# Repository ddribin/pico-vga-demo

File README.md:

This repository contains the KiCad projects for the "VGA, SD card, and  audio demo boards for Raspberry Pi Pico and Raspberry Pi Pico W" from Chapter 3 of ["Hardware design with RP2040"][hw-design].

- `pico_vga_sd_aud`: Pico version
- `picow_vga_sd_aud`: Pico W version

This is based off of Version 2.2 of the document from 14 June, 2023, but contains some minor updates, such as saving with Version 7, the current version of KiCad.

The original KiCad project for the Pico version can be found at: https://datasheets.raspberrypi.com/rp2040/VGA-KiCAD.zip

The original KiCad project for the Pico W version can be found at: https://datasheets.raspberrypi.com/rp2040/VGA-PicoW-KiCAD.zip

The latest version of "Hardware design with RP2040" can be found at: https://datasheets.raspberrypi.com/rp2040/hardware-design-with-rp2040.pdf

[hw-design]: https://datasheets.raspberrypi.com/rp2040/hardware-design-with-rp2040.pdf

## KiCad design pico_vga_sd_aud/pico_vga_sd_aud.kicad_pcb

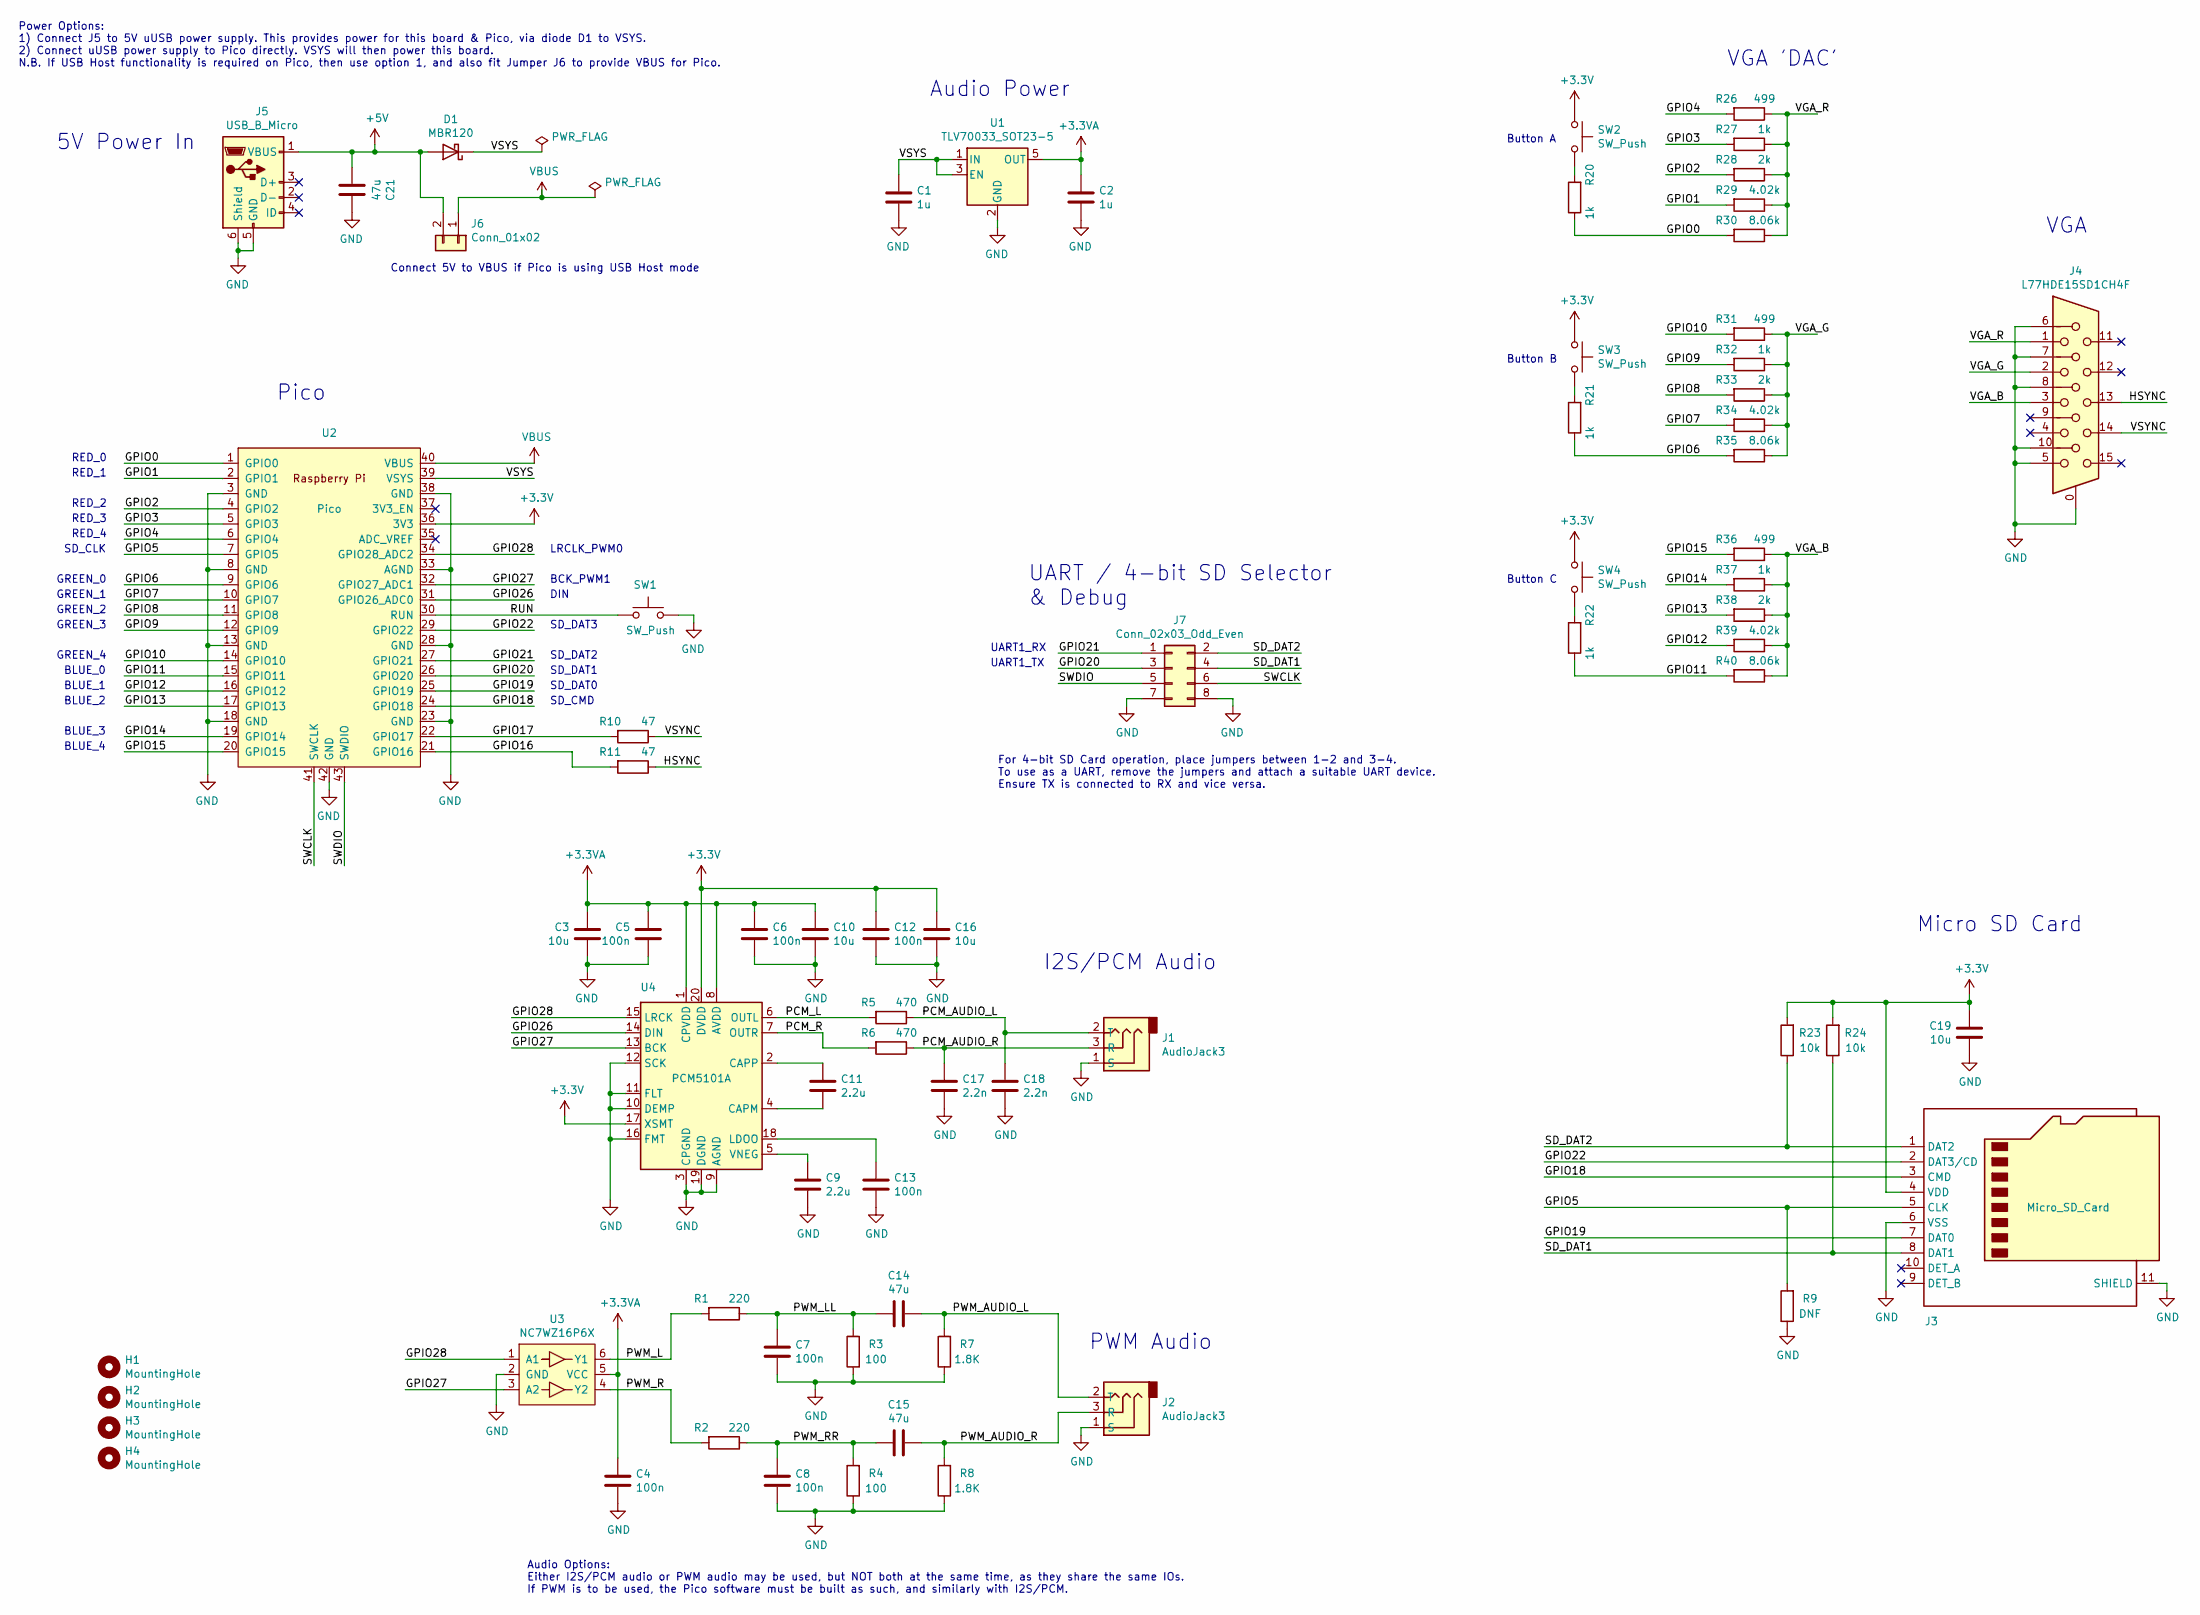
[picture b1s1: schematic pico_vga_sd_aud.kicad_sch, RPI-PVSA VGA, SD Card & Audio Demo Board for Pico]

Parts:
C1, C2: 1u; C_0603_1608Metric
C3, C10, C16, C19: 10u; C_0603_1608Metric
C4, C5, C6, C7, C8, C12, C13: 100n; C_0402_1005Metric
C9, C11: 2.2u; C_0603_1608Metric
C14, C15, C21: 47u; C_0805_2012Metric
C17, C18: 2.2n; C_0402_1005Metric
D1: MBR120; MBR120_SOD-123
H1, H2, H3, H4: MountingHole; MountingHole_2.7mm_M2.5
J1, J2: AudioJack3; CUI_SJ-3523-audio-jack
J3: Micro_SD_Card; microSD_HC_Molex_104031-0811
J4: L77HDE15SD1CH4F; DSUB-15-L77HDE15SD1CH4F
J5: USB_B_Micro; USB_Micro-B_Amphenol_10103594-0001LF_Horizontal_modified
J6: Conn_01x02; PinHeader_1x02_P2.54mm_Vertical
J7: Conn_02x03_Odd_Even; PinHeader_2x04_P2.54mm_Vertical
R1, R2: 220; R_0402_1005Metric
R3, R4: 100; R_0402_1005Metric
R5, R6: 470; R_0402_1005Metric
R7, R8: 1.8K; R_0402_1005Metric
R9: DNF; R_0402_1005Metric
R10, R11: 47; R_0402_1005Metric
R20, R21, R22, R27, R32, R37: 1k; R_0402_1005Metric
R23, R24: 10k; R_0402_1005Metric
R26, R31, R36: 499; R_0402_1005Metric
R28, R33, R38: 2k; R_0402_1005Metric
R29, R34, R39: 4.02k; R_0402_1005Metric
R30, R35, R40: 8.06k; R_0402_1005Metric
SW1, SW2, SW3, SW4: SW_Push; SW_Push_1P1T_NO_Vertical_Wuerth_434133025816
U1: TLV70033_SOT23-5; SOT-23-5
U2: Pico; RPi_Pico_SMD
U3: NC7WZ16P6X; SOT-363_SC-70-6
U4: PCM5101A; TSSOP-20_4.4x6.5mm_P0.65mm

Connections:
+3.3V: C12.1, C16.1, C19.1, J3.4 (VDD), R23.2, R24.2, SW2.1, SW3.1, SW4.1, U2.36 (3V3), U4.17 (XSMT), U4.20 (DVDD)
+3.3VA: C2.1, C3.1, C4.1, C5.1, C6.1, C10.1, U1.5 (OUT), U3.5 (VCC), U4.1 (CPVDD), U4.8 (AVDD)
+5V: C21.2, D1.2 (A), J5.1 (VBUS), J6.2
/GPIO0: R20.1, R30.2, U2.1 (GPIO0)
/GPIO1: R29.2, U2.2 (GPIO1)
/GPIO2: R28.2, U2.4 (GPIO2)
/GPIO3: R27.2, U2.5 (GPIO3)
/GPIO4: R26.2, U2.6 (GPIO4)
/GPIO5: J3.5 (CLK), R9.2, U2.7 (GPIO5)
/GPIO6: R21.1, R35.2, U2.9 (GPIO6)
/GPIO7: R34.2, U2.10 (GPIO7)
/GPIO8: R33.2, U2.11 (GPIO8)
/GPIO9: R32.2, U2.12 (GPIO9)
/GPIO10: R31.2, U2.14 (GPIO10)
/GPIO11: R22.1, R40.2, U2.15 (GPIO11)
/GPIO12: R39.2, U2.16 (GPIO12)
/GPIO13: R38.2, U2.17 (GPIO13)
/GPIO14: R37.2, U2.19 (GPIO14)
/GPIO15: R36.2, U2.20 (GPIO15)
/GPIO16: R11.2, U2.21 (GPIO16)
/GPIO17: R10.2, U2.22 (GPIO17)
/GPIO18: J3.3 (CMD), U2.24 (GPIO18)
/GPIO19: J3.7 (DAT0), U2.25 (GPIO19)
/GPIO20: J7.3, U2.26 (GPIO20)
/GPIO21: J7.1, U2.27 (GPIO21)
/GPIO22: J3.2 (DAT3/CD), U2.29 (GPIO22)
/GPIO26: U2.31 (GPIO26_ADC0), U4.14 (DIN)
/GPIO27: U2.32 (GPIO27_ADC1), U3.3 (A2), U4.13 (BCK)
/GPIO28: U2.34 (GPIO28_ADC2), U3.1 (A1), U4.15 (LRCK)
/HSYNC: J4.13, R11.1
/PCM_AUDIO_L: C18.1, J1.2 (T), R5.1
/PCM_AUDIO_R: C17.1, J1.3 (R), R6.1
/PCM_L: R5.2, U4.6 (OUTL)
/PCM_R: R6.2, U4.7 (OUTR)
/PWM_AUDIO_L: C14.1, J2.2 (T), R7.2
/PWM_AUDIO_R: C15.1, J2.3 (R), R8.2
/PWM_L: R1.2, U3.6 (Y1)
/PWM_LL: C7.1, C14.2, R1.1, R3.2
/PWM_R: R2.2, U3.4 (Y2)
/PWM_RR: C8.1, C15.2, R2.1, R4.2
/RUN: SW1.1, U2.30 (RUN)
/SD_DAT1: J3.8 (DAT1), J7.4, R24.1
/SD_DAT2: J3.1 (DAT2), J7.2, R23.1
/SWCLK: J7.6, U2.41 (SWCLK)
/SWDIO: J7.5, U2.43 (SWDIO)
/VGA_B: J4.3, R36.1, R37.1, R38.1, R39.1, R40.1
/VGA_G: J4.2, R31.1, R32.1, R33.1, R34.1, R35.1
/VGA_R: J4.1, R26.1, R27.1, R28.1, R29.1, R30.1
/VSYNC: J4.14, R10.1
/VSYS: C1.1, D1.1 (K), U1.1 (IN), U1.3 (EN), U2.39 (VSYS)
GND: C1.2, C2.2, C3.2, C4.2, C5.2, C6.2, C7.2, C8.2, C9.2, C10.2, C12.2, C13.2, C16.2, C17.2, C18.2, C19.2, C21.1, J1.1 (S), J2.1 (S), J3.6 (VSS), J3.11 (SHIELD), J4.0, J4.5, J4.6, J4.7, J4.8, J4.10, J5.5 (GND), J5.6 (Shield), J7.7, J7.8, R3.1, R4.1, R7.1, R8.1, R9.1, SW1.2, U1.2 (GND), U2.3 (GND), U2.8 (GND), U2.13 (GND), U2.18 (GND), U2.23 (GND), U2.28 (GND), U2.33 (AGND), U2.38 (GND), U2.42 (GND), U3.2 (GND), U4.3 (CPGND), U4.9 (AGND), U4.10 (DEMP), U4.11 (FLT), U4.12 (SCK), U4.16 (FMT), U4.19 (DGND)
unnamed: R20.2, SW2.2
unnamed: R21.2, SW3.2
unnamed: R22.2, SW4.2
unnamed: C11.2, U4.4 (CAPM)
unnamed: C11.1, U4.2 (CAPP)
unnamed: C13.1, U4.18 (LDOO)
unnamed: C9.1, U4.5 (VNEG)
VBUS: J6.1, U2.40 (VBUS)

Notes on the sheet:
RED_4
RED_0
GREEN_0
SD_CLK
PWM Audio
SD_CMD
SD_DAT3
RED_3
UART1_RX
LRCLK_PWM0
DIN
BLUE_1
VGA
BCK_PWM1
SD_DAT1
GREEN_3
GREEN_2
UART / 4-bit SD Selector & Debug
RED_2
GREEN_4
Audio Options: Either I2S/PCM audio or PWM audio may be used, but NOT both at the same time, as they share the same IOs. If PWM is to be used, the Pico software must be built as such, and similarly with I2S/PCM.
I2S/PCM Audio
Audio Power
Button C
5V Power In
VGA 'DAC'
Button A
SD_DAT0
Power Options: 1) Connect J5 to 5V uUSB power supply. This provides power for this board & Pico, via diode D1 to VSYS. 2) Connect uUSB power supply to Pico directly. VSYS will then power this board. N.B. If USB Host functionality is required on Pico, then use option 1, and also fit Jumper J6 to pro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
Connect 5V to VBUS if Pico is using USB Host mode
Button B
Pico
For 4-bit SD Card operation, place jumpers between 1-2 and 3-4. To use as a UART, remove the jumpers and attach a suitable UART device. Ensure TX is connected to RX and vice versa.
BLUE_4
RED_1
BLUE_3
BLUE_0
UART1_TX
Micro SD Card
GREEN_1

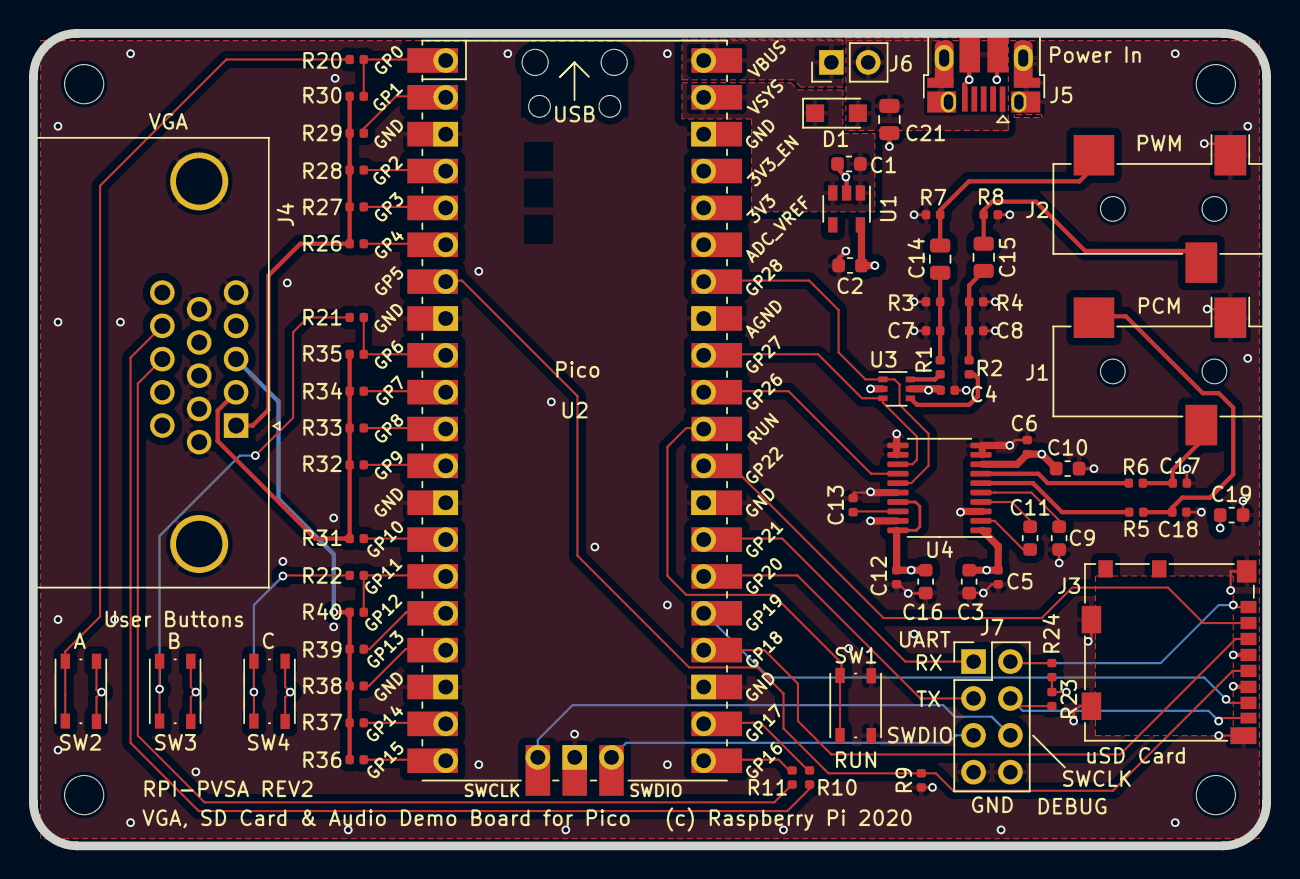
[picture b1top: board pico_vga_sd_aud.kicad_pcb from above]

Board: 4 copper layers, 85.0 x 56.0 mm, 71 parts (0 on the bottom side), 59 nets.

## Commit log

2023-11-24 Initial import of KiCad files
2023-11-24 picow: Save files in KiCad 7.0.9 to upgrade them
2023-11-24 Add README.md
2023-11-24 picow: Update to layer presets
2023-11-24 Start moving Pico symbols and footprints to their own library
2023-11-24 picow: Upgrade project to Verison 7.0.9
    Fix missing symbols. Remove old project files.
2023-11-24 pico: Update footprint to new one with a keepout
    Update symbol to new one
2023-11-24 picow: Update new footprint (with keepout) and symbol
2023-11-25 picow: Get ERC to pass
2023-11-25 pico: Get ERC to pass
2023-11-25 Fix up keepout areas to allow pads under USB
